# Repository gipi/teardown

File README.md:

Repository containing various info about devices analyzed by me.

For analyzed I mean, opened, in some case reversed in hardware and software
and stuffs like that.

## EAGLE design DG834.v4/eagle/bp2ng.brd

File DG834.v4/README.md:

My intention wasn't to install ``openwrt`` but to debrick this router that died three years ago.

Connecting to serial an trying ``tftp`` didn't work so I connected the serial with a ``bus pirate``, I reached the ``CFE``
bootloader and put the system in ``download mode``

```
CFE> d
Download mode ... press enter to stop
```

From a computer connected to the first LAN port i launched the ``nftp`` command

```
# ./nftp -u eth0 DG834GV4_V5.01.16_src/openwrt-dg834gt.img 
Sending frame on eth0 (34:64:a9:75:c6:b6)
Found a router at 12:34:56:ab:cd:ef
Router is a YFM720
Current version is 00
Max upgrade size is 65572 kb
Could not find "magic hardware header" in this image.
Uploading this is not recommended but press Enter if you wish to continue.

Erasing flash, this will take around ten seconds...
Upgrading:    2957312/2957312 bytes
Upload completed, will now verify:
Verifying:    2957312/2957312 bytes
Firmware updated/verified successfully!
```

## Toolchain

It's possible to compile a toolchain for this router using [OpenWRT](http://wiki.openwrt.org/doc/howto/build)

```
$ git clone git://git.openwrt.org/openwrt.git && cd openwrt
$ make menuconfig  # choose Broadcom BCM63xx for ``Target System`` and ``Netgear DG834G v4`` for ``Target Profile``
$ make -j9         # Quad core FTW
```

## UART

Pinout (1)GND, TX, VCC, RX

## JTAG

The connector pad is named ``J201`` a 12 ways, 2 rows with 2mm pitch [board to board connector](http://it.rs-online.com/web/p/file-di-contatti-da-pcb/7656269/)
to be used with an [IDC connector](http://it.rs-online.com/web/p/products/714-2448/).

In order to use the JTAG maybe we have to use the ``buspirate_pullup`` configurations.

Name signal	|Pin out	| Pin out	| Name signal
------------|--------|---------|------------
nTRST	|1	|2	|GND
TDI	|3	|4	|GND
TDO	|5	|6	|GND
TMS	|7	|8	|GND
TCK	|9	|10	|GND
nSRST	|11	|12	|n/a

```
$ openocd -f netgear.cfg
```

```
$ telnet 4444
> targets
    TargetName         Type       Endian TapName            State       
--  ------------------ ---------- ------ ------------------ ------------
 0* bcm6348.cpu        mips_m4k   big    bcm6348.cpu        running
> halt
target state: halted
target halted in MIPS32 mode due to debug-request, pc: 0x8004462c
> mdw 0x8004462C 0x100
0x8004462c: 8fb20018 8fb10014 8fb00010 8c590008 03200008 27bd0020 27bdffe0 afb00010 
0x8004464c: 00a08021 afbf001c afb20018 afb10014 00809021 0c011161 00c08821 8e020028 
0x8004466c: 02402021 02002821 02203021 8fbf001c 8fb20018 8fb10014 8fb00010 8c590004 
0x8004468c: 03200008 27bd0020 27bdffc0 afbe0038 afb40028 afb00018 afbf003c afb70034 
0x800446ac: afb60030 afb5002c afb30024 afb20020 afb1001c 8f830014 3c0207ff 3442ff00 
0x800446cc: 00808021 00c0a021 00e0f021 00621024 00028036 04a30007 3c12bfff 8e1700c4 
0x800446ec: 8e150094 0017bf02 32f70001 080111ca 02a09021 3652ffff 00b29024 0005bf82 
0x8004470c: 2e420004 32f70001 14400004 2415ffff 24020005 164200c7 2403ffea 8e820000 
0x8004472c: 044000c4 2403ffea 28440064 108000c1 2656ffff 2ed60002 0002102b 16c200be 
0x8004474c: 8fbf003c 13c0002e 00000000 0c00ace3 24040017 144000c4 00000000 52c00011 
0x8004476c: 8e020094 8e020354 8e030094 8c4201d0 52430004 8e830000 104000ae 2403ffff 
0x8004478c: 8e830000 8e040024 0083202b 50800005 8e020094 0043102b 144000a6 2403ffff 
0x800447ac: 8e020094 24030005 14430008 00000000 12420006 02002021 8e05001c 0c0110db 
0x800447cc: 24a5ff88 1040009b 2403ffff 0c011085 02002021 10400097 2403ffff 8e0200c4 
0x800447ec: 3c041000 00821024 1040009f 00000000 16e0009d 8fbf003c 08011292 00601021 
0x8004480c: 40116000 3621001f 3821001f 40816000 00000040 00000040 00000040 000000c0 
0x8004482c: 3c13802d 2662cd98 8c4203dc 1602000d 32230001 40016000 32310001 3421001f 
0x8004484c: 3821001f 02218825 40916000 00000040 00000040 00000040 000000c0 08011290 
0x8004486c: 2403ffea 8e020094 56420015 2403ffff 12c00005 00000000 8e850000 8e040024 
0x8004488c: 54a4000f 2403ffff 40016000 32310001 3421001f 3821001f 02218825 40916000 
0x800448ac: 00000040 00000040 00000040 000000c0 54600060 00001821 08011291 8fbf003c 
0x800448cc: 12a3000f 2664cd98 52a2000e 8c9e03d4 40016000 32310001 3421001f 3821001f 
0x800448ec: 02218825 40916000 00000040 00000040 00000040 000000c0 080111bb 8e1700c4 
0x8004490c: 8c9e03d4 8e020014 021ef026 afa20010 10400004 2fde0001 02002821 0c01117d 
0x8004492c: 00003021 53c00007 8e0300c4 8e020028 2664cd98 8c42001c 0040f809 02002821 
0x8004494c: 8e0300c4 3c02efff 3442ffff 0017bf00 00621024 0057b825 ae1700c4 8e860000 
0x8004496c: 02002021 02402821 8e160018 0c0110bd 8e150028 13c00006 8fa20010 8e020028 
0x8004498c: 8c420020 0040f809 2664cd98 8fa20010 50400006 8e020028 2664cd98 02002821 
0x800449ac: 0c011191 00003021 8e020028 52a2000e 8e020018 8ea2002c 50400005 8e020028 
0x800449cc: 2664cd98 0040f809 02002821 8e020028 2664cd98 8c420030 0040f809 02002821 
0x800449ec: 08011283 00000000 12c20005 2664cd98 8ea20034 02002821 0040f809 02c03021 
0x80044a0c: 40016000 32310001 3421001f 3821001f 02218825 40916000 00000040 00000040
> dump_image DG834.v4/flash.raw 0xbfc00000 0x00400000                  |
dumped 4194304 bytes in 37076.000000s (0.110 KiB/s)
```

Links
-----

 - https://wiki.openwrt.org/toh/netgear/dg834g.v4
 - http://hexblog.com/files/recon%202010%20Skochinsky.pdf
 - http://www.ece.gatech.edu/academic/courses/ece2035/readings/embedded/MIPSvsARM.pdf
 - https://jaforeck.wordpress.com/2012/08/09/bricked-ebook-reader-bus-pirate-openocd-working-ebook-reader-14/
 - http://alvarop.com/2013/02/debugging-arm-cortex-m3-devices-with-gdb-and-openocd/
 - http://dangerousprototypes.com/docs/Gonemad%27s_Bus_Pirate/OpenOCD_walk_through
 - http://dangerousprototypes.com/forum/viewtopic.php?t=295
 - https://tux4u.wordpress.com/tag/bus-pirate/

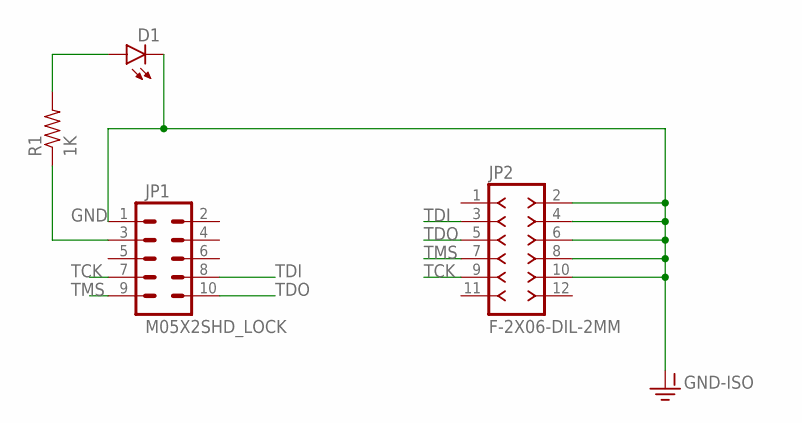
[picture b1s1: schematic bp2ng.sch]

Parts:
D1: LED1206; LED-1206
JP1: M05X2SHD_LOCK; 2X5-SHROUDED_LOCK
JP2: F-2X06-DIL-2MM; DIL-2MM-2X06
R1: 1K; 1206

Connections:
GND: D1.C, JP1.1, JP2.2, JP2.4, JP2.6, JP2.8, JP2.10
unnamed: D1.A, R1.2
unnamed: JP1.3, R1.1
TCK: JP1.7, JP2.9
TDI: JP1.8, JP2.3
TDO: JP1.10, JP2.5
TMS: JP1.9, JP2.7

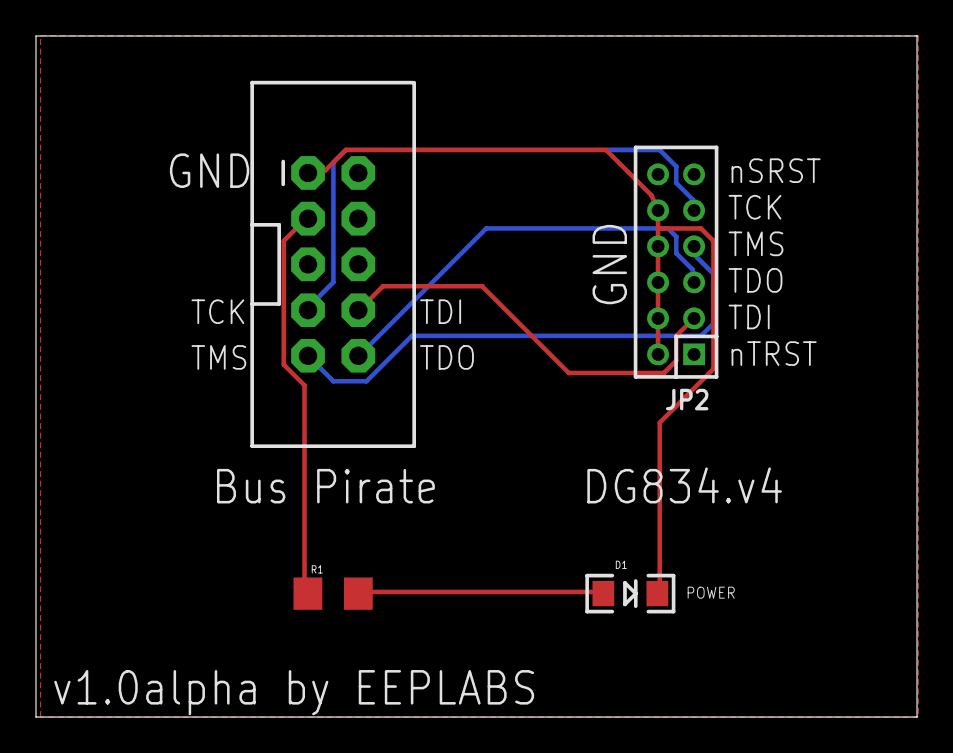
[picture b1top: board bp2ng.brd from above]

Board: 2 copper layers, 48.9 x 37.8 mm, 4 parts (0 on the bottom side), 7 nets.

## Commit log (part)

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2015-02-25 Initial import.
2015-02-25 Add SP-H03.
2015-02-25 Add Polaroid device.
2015-02-25 Add connectors' codes.
2015-02-25 Find out the SOC for the PICO.
2015-02-25 Add DG834.v4 device.
2015-02-25 Some notes about JTAG.
2015-02-25 Add log messages.
2015-02-26 Update the disassembly of second stage bootloader.
2015-03-18 Add pinout of JTAG.
2015-03-19 Add Eagle CAD files.
2015-05-09 Add configuration file for JTAG.
2015-05-12 Add link.
2015-05-13 Add note about OpenWRT toolchain building.
2015-09-07 Add images for seagate.
2015-10-06 Add new subdirectory about CDs.
2016-06-11 Add TC-071MC teardown.
2016-06-11 Add note.
2016-06-12 Add info about dumped partitions.
2016-06-13 Add header.
2016-06-13 Add note about images.
2016-06-13 Fix typo.
2016-06-15 Add serial port information.
2016-06-19 Update w note about FIQ.
2016-06-20 Update adventure.
2016-11-30 Add TODO.
2016-12-24 Add a skeleton for radare2 configuration file
2016-12-25 DG834.v4: add zignature file.
2017-01-07 HG553: first working(?) openocd+buspirate configurations.
2017-01-07 hg533: add notes about CPU single stepping.
2017-01-08 hg553: add note about painful process of JTAGging.
2017-01-08 hg553: add well-known debrick software.
2017-01-08 DG834: improve r2 script file.
2017-01-08 DG834: add serial pinout.
2017-01-10 hg553: add some notes.
2017-01-10 hg553: add note about dumping CFE from memory.
2017-01-10 hg553: add link.
2017-01-13 Add note about mips segmentation.
2017-01-15 DG834.v4: add makefile to build elf from raw images.
2017-01-15 DG834.v4: fix OpenWRT link.
2017-01-15 DG834.v4: fix flash openocd configuration.
2017-01-16 HG553: finally configured the flash under OpenOCD.
2017-05-26 DSL-302T: add page.
2017-05-26 DSL-302T: add more infos.
2017-06-29 One day I will explain.
2017-07-02 DSL-302T: improvement.
2017-07-03 DSL-302T: add initial boot log.
2017-07-03 Add dump_image script.
    Helps to dump a binary image from a device from JTAG.
2017-07-03 dump_image: add some options.
2017-07-06 HG553: fix pinout.
2017-07-09 DSL-302T: add bootloader dumping.
2017-07-09 HG553: add headerless cfe.
2017-07-09 HG553: add OpenOCD configuration file that uses rpi as adapter.
2017-07-09 HG553: add note about using rpi.
2017-08-14 Add alcatel page.
2017-08-18 Add MiraScreen section.
2017-08-19 mirascreen: some information gathering.
2017-08-19 Mirascreen: add advancement into analysis.
2017-08-20 mirascreen: improvement a gogo.
2018-02-28 Add skeleton for ZSun.
2018-02-28 ZSun: update.
2018-04-21 Polaroid: add (incomplete) list of chips.
2018-04-21 Add meta/ with info about SoC and stuffs.
2018-04-27 Improve Rockchip.
2018-11-04 Pico: some progress.
2018-11-04 Fix formatting.
2019-02-10 pico-sp-h03: update README.
2019-02-17 Pico SP-H03: add initial analysis of the bootloader code.
2019-02-18 Pico SP-H03/add radare2 project file and improve reversing.
2019-02-19 Pico SP-H03: update bootlader analysis.
2019-02-20 Fix offset
2019-02-21 Pico SP-H03: improve explanation about USB boot modes.
2019-02-22 Pico SP-H03: improve formatting and fix typo.
2019-02-23 mirascreen: add filesystem supported.
2019-02-23 Pico SP-H03: add more information about USB boot mode.
    Also import and modify the tcctool from the rockbox project.
2019-02-23 Pico SP-H03: reorganize writeup.
2019-02-24 Pico SP-H03: add complete list of the files contained in the update archive.
2019-02-24 Pico SP-H03: add note about Cowon v5 using the same SoC.
2019-02-24 Pico SP-H03: using naming more aligned to the documentation.
    Also add more log during the flashing.
2019-02-25 Pico SP-H03: first attempt to write bare metal ARM code.
2019-03-02 Pico SP-H03: use the same order as the TC76xx.
2019-03-02 Pico SP-H03: Use 0x00001000 as base address.
2019-03-02 Pico: make code more readable.
2019-03-02 Pico: try to enable PMU watchdog.
    THIS SEEMS TO CASE THE USB TO DISCONNECT AFTER A FEW SECONDOS!
2019-03-02 Pico: add routine to power off the CPU.
2019-03-02 Pico: factorize code to enable watchdog.
2019-03-02 Pico: first attempt to exfill GPIOs physical position toggling them.
2019-03-03 Pico: fix lr-saving registers.
2019-03-03 Pico: add watchdog_clear routine.
2019-03-03 Pico: move constant nearer to the routine uses it.
2019-03-03 Pico: modify main routine to enable watchdog and then start GPIO identification.
2019-03-03 Pico: fix encoding.
    Pratically we want to use the group number to be the MSB.
2019-03-03 Pico: clear the watchdog after each iteration of the GPIO toggling.
2019-03-03 Pico: TP1101 now at GND level.
2019-03-03 Pico: add delay routine.
2019-03-04 Pico/tcc-emu: emulate firmware mmapping it.
2019-03-04 Pico: expose symbols for the firmware.
2019-03-04 Pico/tccvirus: fix trashing r8 register.
    The ARM instruction set allows to use left shift inside an instruction.
2019-03-04 Pico/tccvirus: fix comparison logic.
    We to add after the comparison otherwise for the first case the loop
    wraps to 32bit digit.
2019-03-04 Pico/tccvirus: clear the watchdog less frequently.
2019-03-04 Pico/tccvirus: improve formatting.
2019-03-04 Pico/tccvirus: add after comparing.
2019-03-04 Pico/tccvirus: improve code.
2019-03-06 Pico: start quest for GPIOs recovery.
2019-03-23 Pico: add initial analysis of the UART configuration.
2019-03-24 Pico: add serial pinout and boot log.
2019-03-26 Pico: finally some interaction via serial port.
2019-03-26 Pico: add call to toggle GPIOs.
2019-04-07 Add Meraki MX64.
2019-04-07 Add script to dump a file from the serial line.
2019-04-08 Add serial upload script.
2019-04-09 meraki-mx64: add more info.
2019-04-09 serial_upload: rework and add a progress bar.
    Now it logs the communications in a separate file.
2019-04-10 meraki: add (not working) openocd configuration.
    The output is
    Open On-Chip Debugger 0.10.0
    Licensed under GNU GPL v2
    For bug reports, read
    http://openocd.org/doc/doxygen/bugs.html
    adapter speed: 1000 kHz
2019-04-12 Mirascreen: add ghidra.
2019-04-14 Create directory for tools.
2019-04-14 MiraScreen: further analysis.
2019-04-15 MiraScreen: add link for MFC reversing.
2019-04-15 MiraScreen: add some info from reversing with Ghidra.
2019-05-05 Mirascreen: update Ghidra.
2019-05-12 Mirascreen: add some notes.
2019-06-23 MiraScreen: first working checksum calculator for the Actions firmwares.
2019-06-23 MiraScreen: actions-tools now decompress FIRM.
2019-09-10 DSL-2640B: new device.
2019-09-25 DSL-2640B: add info about firmware.
2019-09-29 MiraScreen: add some notes about thttpd.
2019-09-30 MiraScreen: fix procedure to enter download mode.
2019-09-30 MiraScreen: more USB protocol reversing.
2019-10-01 MiraScreen: improve USB reversing.
2019-10-02 Add CBW to (probably) close the connection.
2019-10-04 MiraScreen: update flash script with FWSC functionality.
2019-10-06 MiraScreen: dump MBR.
2019-10-30 TL-WR841N: add new device.
2019-10-30 TL-WR841N: add notes about firmware and simple tool extracted from openWRT
2019-10-31 MiraScreen: more stuff.
2019-10-31 TL-WR841N: update info.
2019-11-02 tools: add usage to serial_upload.py.
2020-01-10 TL-WR841N: add note about emulation.
2020-01-15 Add some precompiled mips binaries.
2020-01-15 TL-WR841N: improve README.
2020-02-17 TL-WR841N: add notes about tftp.
2020-03-12 Add new device.
2020-03-23 michelin: add code to fuzz.
2020-03-24 actions-tools: now unpack firmwares.
2020-04-12 michelin: finally extract useful information from the board.
2020-04-12 Add LD_PRELOAD trick related files.
    Shamelessly stolen from the project ldpreloadhook.
2020-04-13 actions/adfu: improve logging.
2020-04-14 meta/actions: import rockbox adfu related program.
2020-04-16 meta/actions: add decryption algorithm.
2021-06-28 Add powkiddy.
2021-07-07 Some updates on the booting process reversing.
2021-07-10 powkiddy: improve reversing.
2021-07-21 powkiddy: first failed attempts to create bare metal uart logger.
2021-07-21 Add missing script.
2021-07-21 PowKiddy: add more info.
2021-07-22 PowKiddy: serial now is working.
2021-07-27 PowKiddy: improve Q700 script for dumping.
2021-07-27 PowKiddy: add BROM analysis.
2021-07-27 PowKiddy: add note.
2021-07-28 PowKiddy: move bare metal to its own directory.
2021-07-31 PowKiddy: it's possible to use trimmed down ADEC file.
2021-07-31 PowKiddy/baremetal: add missing files and improve Makefile.
2021-07-31 PowKiddy: usb baremetal is not working.
2021-07-31 PowKiddy/baremetal: add example code to hijack exceptions/irqs vector table.
2021-08-04 open-adec: improve hexdump.
    Now add a space between hex digits.
2021-08-04 open-adec: hard fix on irq1 entry.
2021-08-04 open-adec: dump first sector from flash via serial.
2021-08-04 meta/actions/adfu: improve module.
2021-08-04 open-adec: improve Cause exception parsing.
2021-08-04 open-adec: compile with debugging symbols.
    This helps when you want to debug an exception, using addr2line.
2021-08-06 open-adec: add dependency to adfuload.
2021-08-09 open-adec: add minimal assert functionality.
    For now the line number is not available, since I would prefer waiting
    on implementing a sprintf that showing an hexadecimal number as new line.
2021-08-10 open-adec: improve prologue-epiloque usb IRQ.
2021-08-10 open-adec: add printf-like methods.
2021-08-10 open-adec: show board information with the banner.
2021-08-10 powkiddy: add ghidra's script for convert ZLF to ELF.
2021-08-10 open-adec: remove temporary stuff.
2021-08-10 meta/actions/adfuload: fix old commit.
2021-08-10 open-adec: create "oa", a tool to dump flash and other things.
2021-08-10 open-adec: use general exception handling also for TLB refill.
2021-08-11 open-adec: improve oa and fix dependencies.
2021-08-12 PowKiddy: add ghidra script to resolve syscalls for the ucos-II.
2021-08-12 PowKiddy: add README for ghidra scripts.
2021-08-19 open-adec: reorganize source files.
2021-08-19 open-adec: it seems to work with the mirascreen.
    Obviously we must rework again for the powkiddy :)
2021-08-19 open-adec/oa: update call to adfu module.
2021-08-19 open-adec: multi-board compilation.
2021-08-19 adfu module reorganization.
2021-08-28 open-adec: improve USB stack.
2021-08-28 open-adec: rework config variables.
2021-08-28 open-adec: improve Makefile.
2021-08-28 open-adec: improve BANNER.
    Now with the real BOARD value.
2021-08-28 open-adec: assert as preprocessing statement.
    In this way we preserve the actual point where is triggered and don't lose
    the calling context.
2021-08-28 open-adec: fix AM8252's BROM related code.
2021-08-28 open-adec: use "li" instead of %hi/%lo.
2021-08-28 open-adec: update README.
2021-08-28 open-adec: improve Makefile.
    Also generate the stack usage report files (with extension ".su").
2021-08-28 open-adec: improve banner.
2021-08-28 open-adec: add a stacktrace CBW command.
    It's useful to debug the actual state of the system on the fly.
2021-08-28 open-adec: implement dump memory command via USB.
2021-08-28 open-adec: move data and rodata in the available space before irqs.
2021-10-06 Add KR.YL's flash datasheet.
2021-10-27 Add Kobo Touch.
2021-12-13 Michelin: add PCB scan.
2021-12-13 Powkiddy and Kobo Touch: add notes.
2022-02-21 Add Remarkable2.
2022-03-31 Add AGPTEK-R2S.
2022-04-01 AGPTEK-R2S: add note about reset signal.
2022-04-01 AGPTEK: Add note about flash and FM receiver.
2022-04-01 tools: add hydra_spi_dump script.
    Tools directly from the hydrabus repo, modified to handle multiple reads.
    Very HACKY.
2022-07-21 Remarkable 2: add ss script.
2024-05-03 build(deps): bump tqdm from 4.23.4 to 4.66.3
    Bumps [tqdm](https://github.com/tqdm/tqdm) from 4.23.4 to 4.66.3.
    - [Release notes](https://github.com/tqdm/tqdm/releases)
    - [Commits](https://github.com/tqdm/tqdm/compare/v4.23.4...v4.66.3)
    ---
    updated-dependencies:
    - dependency-name: tqdm

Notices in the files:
parts and their libraries:
SparkFun-Connectors: Licensing: Creative Commons ShareAlike 4.0 International - https://creativecommons.org/licenses/by-sa/4.0
con-headers-jp: Copyright (C) 2008, Bob Starr
